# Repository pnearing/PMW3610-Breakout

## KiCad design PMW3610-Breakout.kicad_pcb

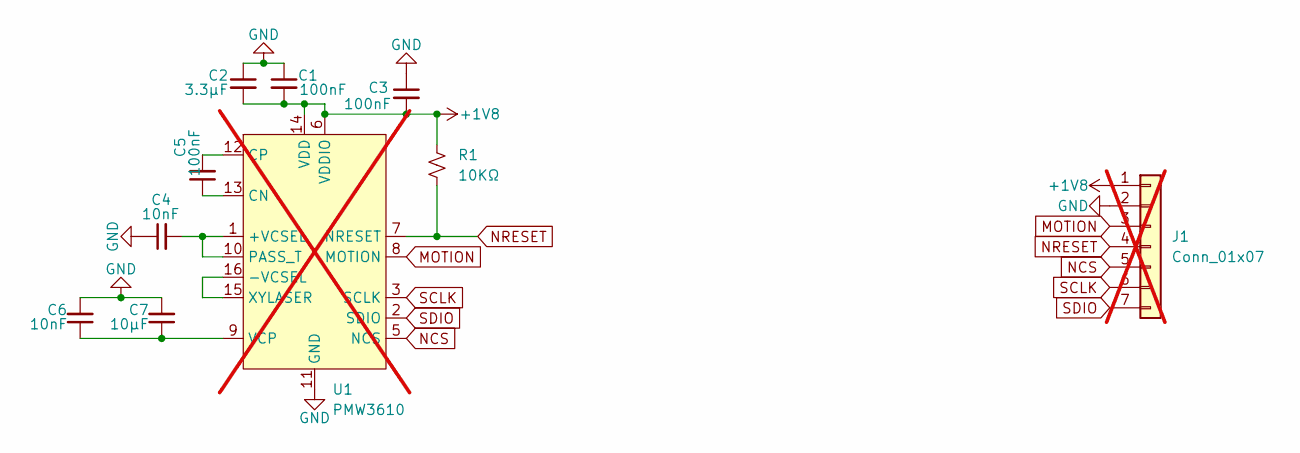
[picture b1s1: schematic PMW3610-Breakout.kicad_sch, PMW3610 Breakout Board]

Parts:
C1, C3, C5: 100nF; C_0603_1608Metric_Pad1.08x0.95mm_HandSolder; LCSC Part # C66501
C2: 3.3µF; C_0603_1608Metric_Pad1.08x0.95mm_HandSolder; LCSC Part # C237213
C4, C6: 10nF; C_0603_1608Metric_Pad1.08x0.95mm_HandSolder; LCSC Part # C519406
C7: 10µF; C_0603_1608Metric_Pad1.08x0.95mm_HandSolder; LCSC Part # C6119849
J1: Conn_01x07; PinHeader_1x07_P2.54mm_Vertical; LCSC Part # C6332200; not fitted
R1: 10KΩ; R_0603_1608Metric_Pad0.98x0.95mm_HandSolder; LCSC Part # C2906982
U1: PMW3610; PMW3610DM-SUDU 16Pin; not fitted

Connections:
+1V8: C1.2, C2.2, C3.2, J1.1, R1.1, U1.6 (VDDIO), U1.14 (VDD)
GND: C1.1, C2.1, C3.1, C4.1, C6.2, C7.2, J1.2, U1.11 (GND)
MOTION: J1.3, U1.8 (MOTION)
NCS: J1.5, U1.5 (NCS)
NRESET: J1.4, R1.2, U1.7 (NRESET)
unnamed: C4.2, U1.1 (+VCSEL), U1.10 (PASS_T)
unnamed: U1.15 (XYLASER), U1.16 (-VCSEL)
unnamed: C5.1, U1.13 (CN)
unnamed: C5.2, U1.12 (CP)
unnamed: C6.1, C7.1, U1.9 (VCP)
SCLK: J1.6, U1.3 (SCLK)
SDIO: J1.7, U1.2 (SDIO)

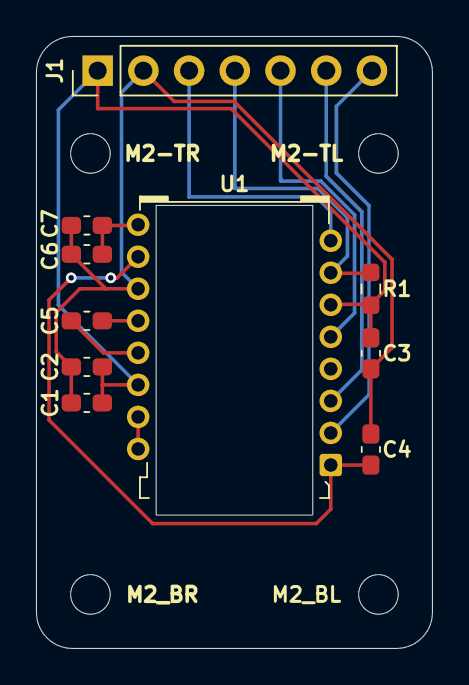
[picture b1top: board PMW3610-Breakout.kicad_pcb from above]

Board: 2 copper layers, 22.0 x 34.0 mm, 14 parts (0 on the bottom side), 12 nets.

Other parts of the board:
M2-TL, M2-TR, M2_BL, M2_BR: MountingHole_2.2mm_M2
